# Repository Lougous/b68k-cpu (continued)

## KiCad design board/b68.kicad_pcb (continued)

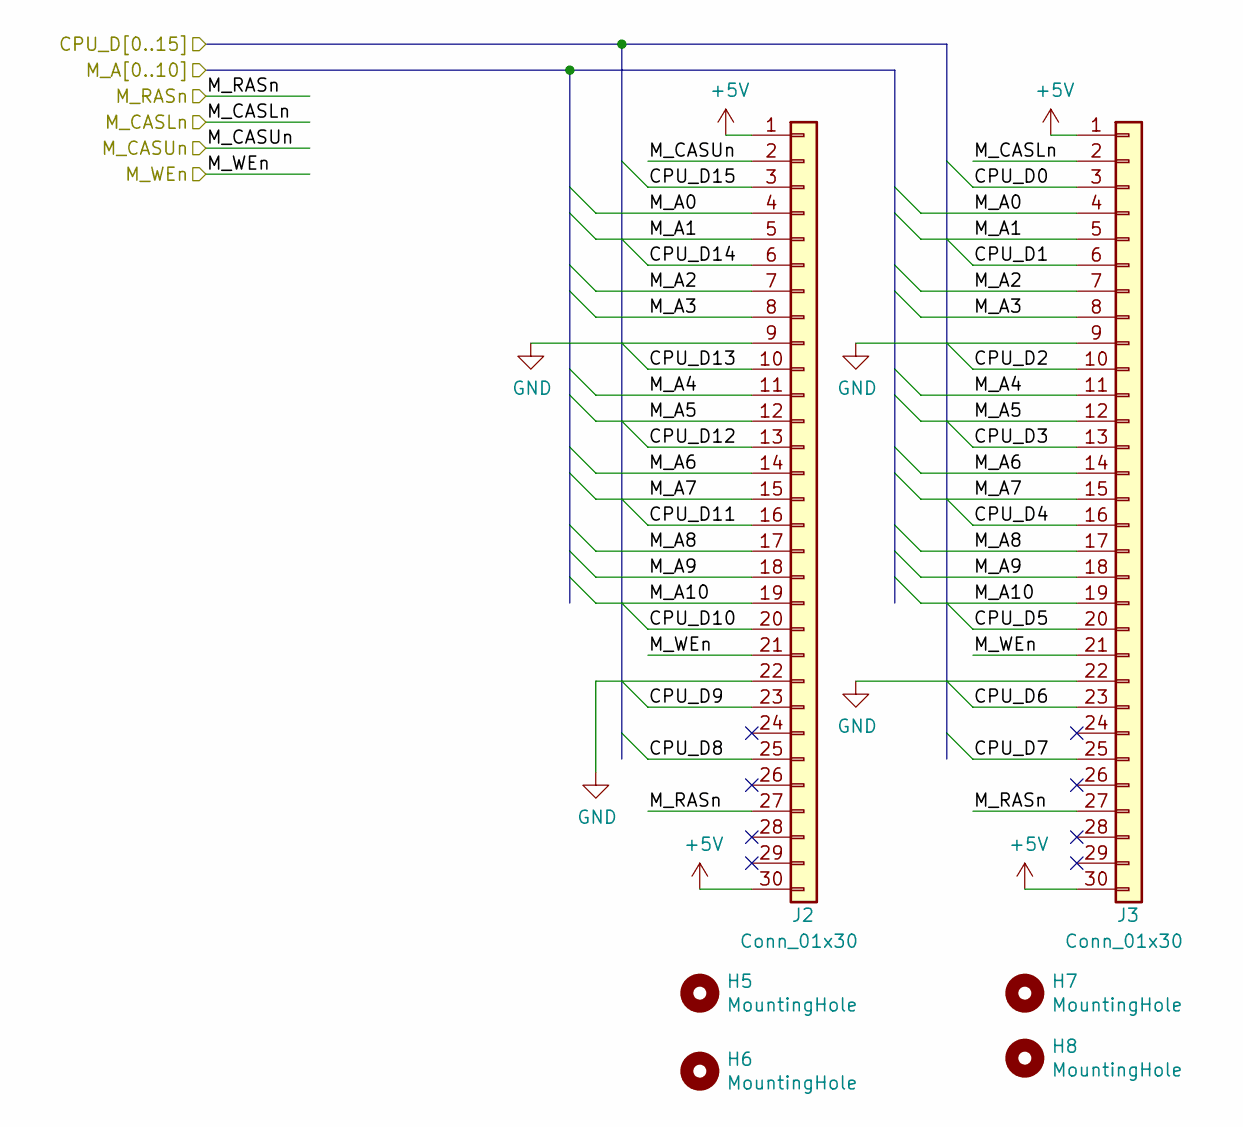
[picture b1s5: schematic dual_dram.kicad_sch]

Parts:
H5, H6, H7, H8: MountingHole; MountingHole_2.7mm_M2.5_DIN965_Pad
J2, J3: Conn_01x30; PinHeader_1x30_P2.54mm_Vertical

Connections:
+5V: J2.1, J2.30, J3.1, J3.30; also elsewhere on the board
/CPU_D0: J3.3; also elsewhere on the board
/CPU_D1: J3.6; also elsewhere on the board
/CPU_D2: J3.10; also elsewhere on the board
/CPU_D3: J3.13; also elsewhere on the board
/CPU_D4: J3.16; also elsewhere on the board
/CPU_D5: J3.20; also elsewhere on the board
/CPU_D6: J3.23; also elsewhere on the board
/CPU_D7: J3.25; also elsewhere on the board
/CPU_D8: J2.25; also elsewhere on the board
/CPU_D9: J2.23; also elsewhere on the board
/CPU_D10: J2.20; also elsewhere on the board
/CPU_D11: J2.16; also elsewhere on the board
/CPU_D12: J2.13; also elsewhere on the board
/CPU_D13: J2.10; also elsewhere on the board
/CPU_D14: J2.6; also elsewhere on the board
/CPU_D15: J2.3; also elsewhere on the board
/M_A0: J2.4, J3.4; also elsewhere on the board
/M_A1: J2.5, J3.5; also elsewhere on the board
/M_A2: J2.7, J3.7; also elsewhere on the board
/M_A3: J2.8, J3.8; also elsewhere on the board
/M_A4: J2.11, J3.11; also elsewhere on the board
/M_A5: J2.12, J3.12; also elsewhere on the board
/M_A6: J2.14, J3.14; also elsewhere on the board
/M_A7: J2.15, J3.15; also elsewhere on the board
/M_A8: J2.17, J3.17; also elsewhere on the board
/M_A9: J2.18, J3.18; also elsewhere on the board
/M_A10: J2.19, J3.19; also elsewhere on the board
/M_CASLn: J3.2; also elsewhere on the board
/M_CASUn: J2.2; also elsewhere on the board
/M_RASn: J2.27, J3.27; also elsewhere on the board
/M_WEn: J2.21, J3.21; also elsewhere on the board
GND: J2.9, J2.22, J3.9, J3.22; also elsewhere on the board

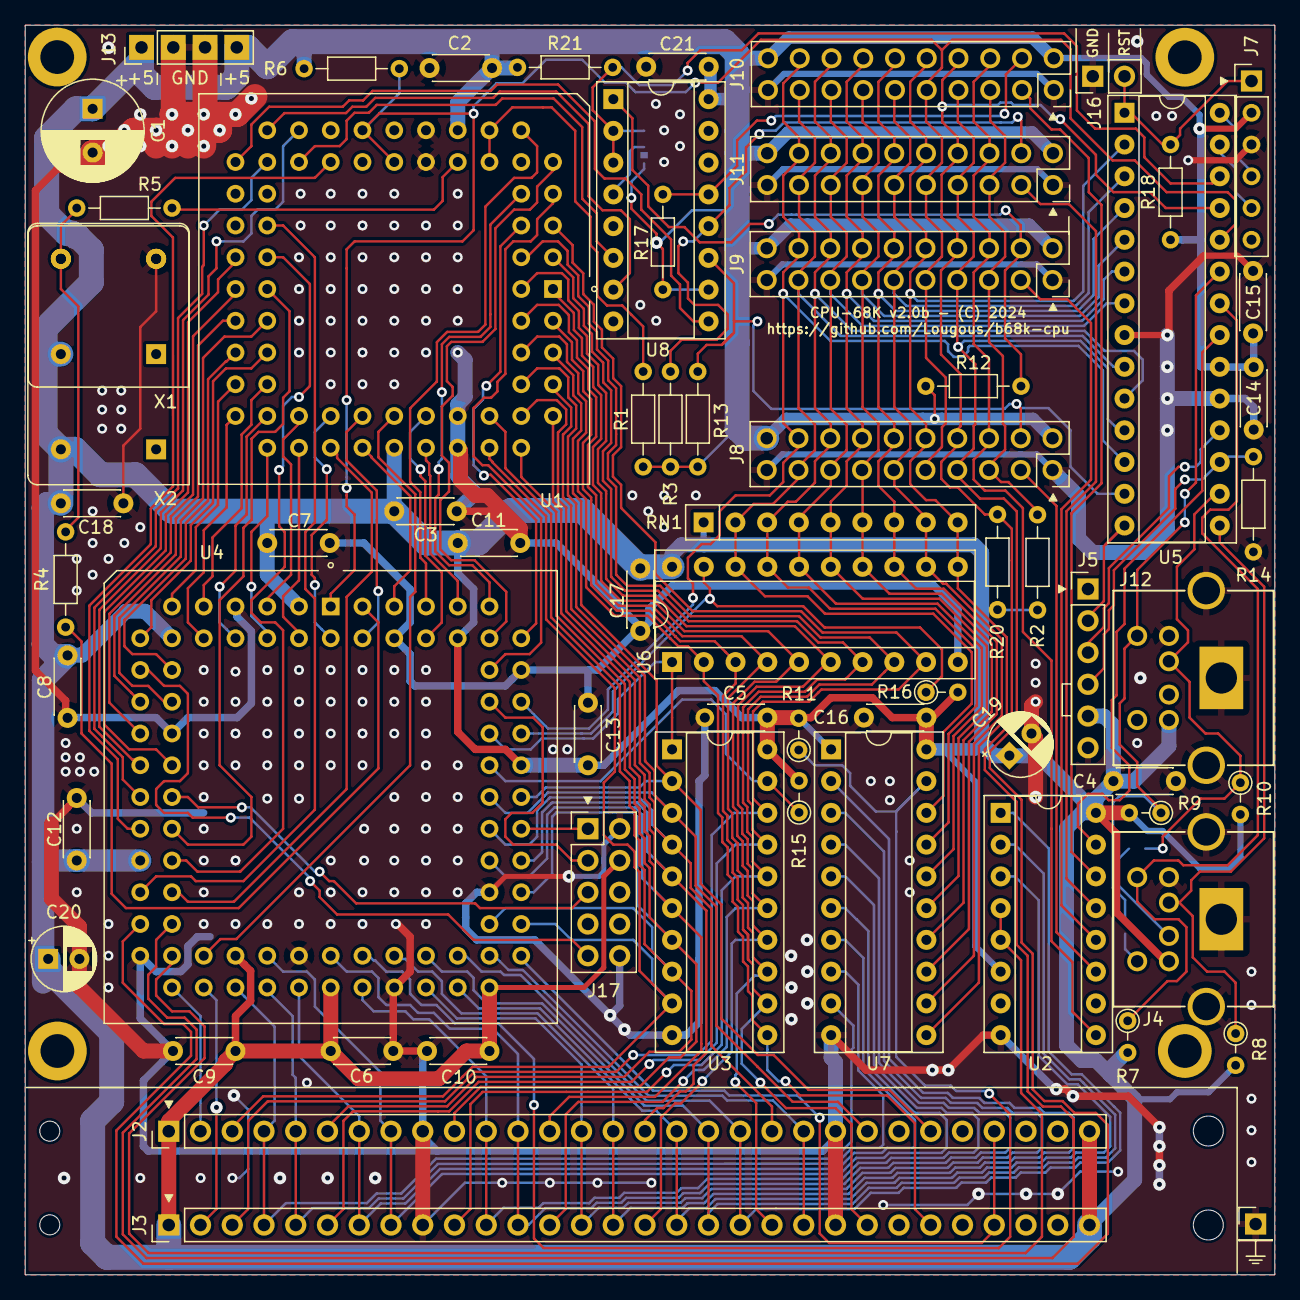
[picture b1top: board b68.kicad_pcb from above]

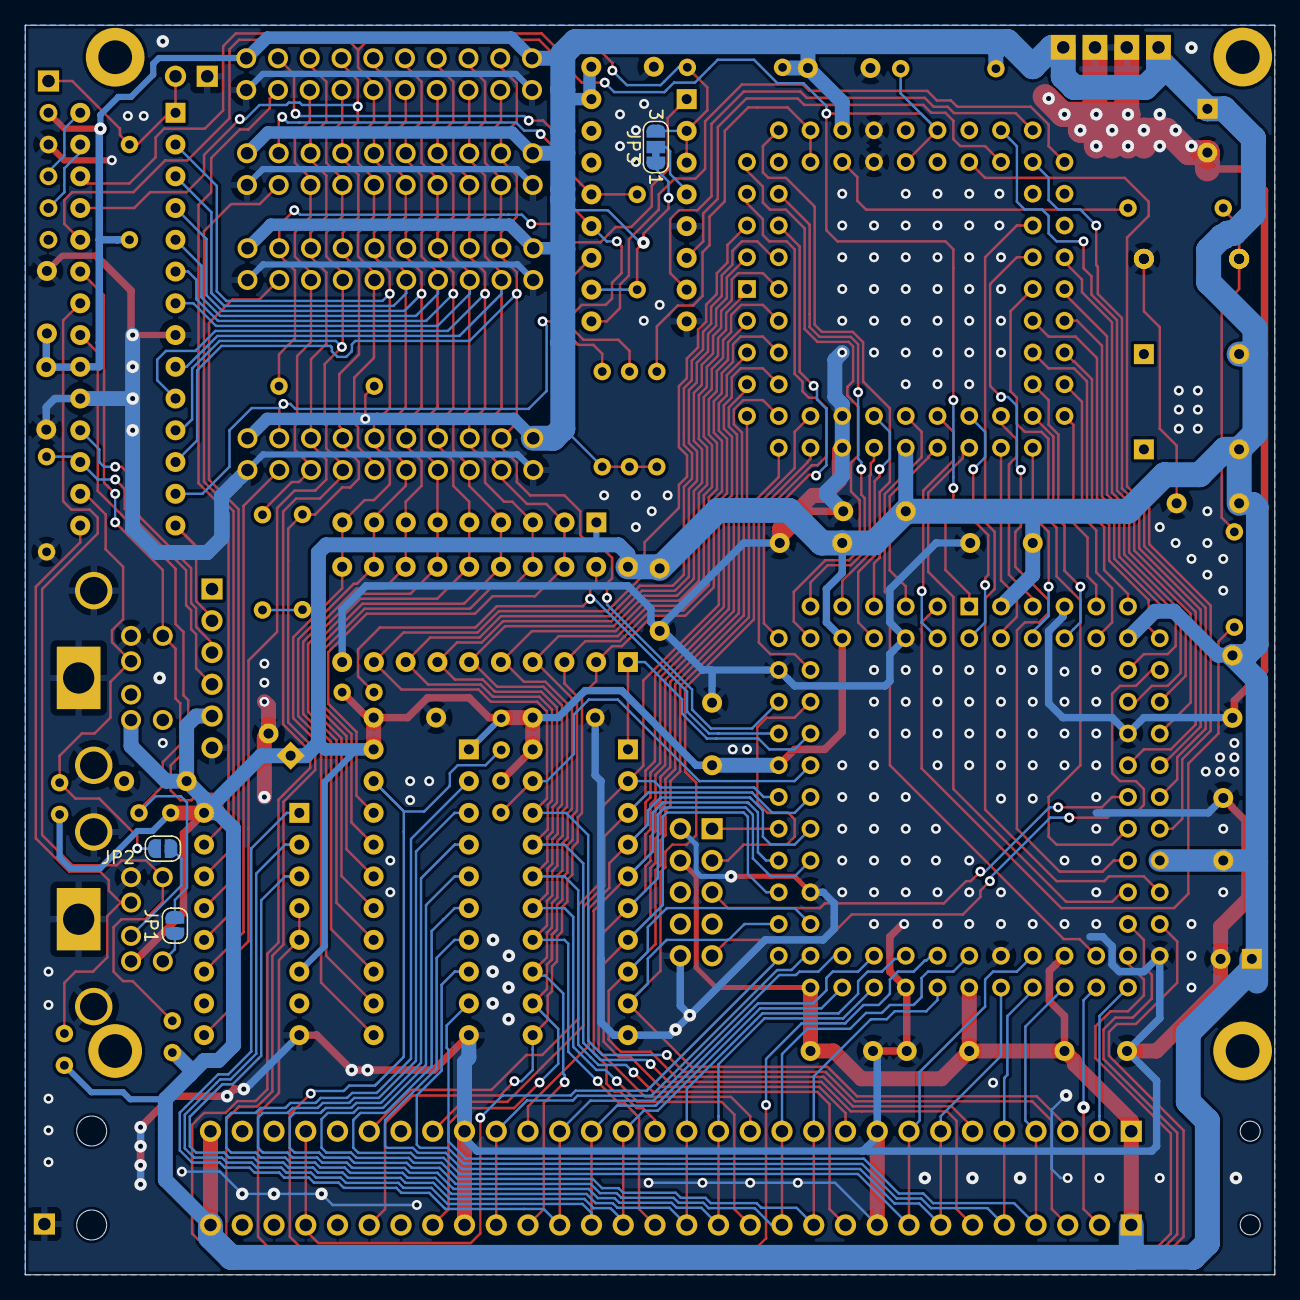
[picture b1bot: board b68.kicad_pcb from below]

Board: 2 copper layers, 100.0 x 100.0 mm, 77 parts (3 on the bottom side), 117 nets.

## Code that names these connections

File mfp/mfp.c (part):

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#pragma config FCMEN = ON       // Fail-Safe Clock Monitor Enable bit (Fail-Safe Clock Monitor enabled)

// CONFIG2L
#pragma config MCLRE = EXTMCLR  // MCLR Enable bit (If LVP = 0, MCLR pin is MCLR; If LVP = 1, RE3 pin function is MCLR )
#pragma config PWRTS = PWRT_OFF // Power-up timer selection bits (PWRT is disabled)
#pragma config MVECEN = ON      // Multi-vector enable bit (Multi-vector enabled, Vector table used for interrupts)
#pragma config IVT1WAY = ON     // IVTLOCK bit One-way set enable bit (IVTLOCK bit can be cleared and set only once)
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    U1TXB = data;                     // send one character
}

#define CEn              (PORTBbits.RB0)

#define RSTn             (PORTBbits.RB3)
#define ASSERT_RSTn      TRISBbits.TRISB3 = 0;   // output - RST# asserted
#define DEASSERT_RSTn    TRISBbits.TRISB3 = 1;   // input - RST# deasserted

#define ACKn             (PORTBbits.RB4)
#define ASSERT_ACKn      TRISBbits.TRISB4 = 0;   // output - ACK# asserted
#define DEASSERT_ACKn    TRISBbits.TRISB4 = 1;   // input - ACK# deasserted

#define IRQn             (PORTBbits.RB5)
#define ASSERT_IRQn      TRISBbits.TRISB5 = 0;   // output - IRQ# asserted
#define DEASSERT_IRQn    TRISBbits.TRISB5 = 1;   // input - IRQ# deasserted

#define WEn              (PORTCbits.RC0)

#define A0               (PORTCbits.RC1)

#define SYS_IRQn             (PORTCbits.RC2)
#define ASSERT_SYS_IRQn      TRISCbits.TRISC2 = 0;   // output - IRQ# asserted
#define DEASSERT_SYS_IRQn    TRISCbits.TRISC2 = 1;   // input - IRQ# deasserted

//#define IOEXT0           (PORTCbits.RC2)
#define IOEXT1           (PORTCbits.RC3)
#define IOEXT2_TX        (PORTCbits.RC7)
#define IOEXT3_RX        (PORTCbits.RC6)

#define BSTP             IOEXT3_RX

#define KB_DAT           (PORTCbits.RC4)
#define KB_CLK           (PORTBbits.RB1)

#define MS_DAT           (PORTCbits.RC5)
#define MS_DAT_DIR       (TRISCbits.TRISC5)

#define MS_CLK           (PORTBbits.RB2)
#define MS_CLK_DIR       (TRISBbits.TRISB2)

// boot file content
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
#if 0
    //set uart 1 pins to extension connector (J5)
    // TX: RC7 (pin 18)
    TRISCbits.TRISC7 = 0;   // output
    RC7PPS=0b00010011;
  
    // RX: RC6 (pin 17)
    TRISCbits.TRISC6 = 1;   // input
    U1RXPPS=0b00010110;
#else
    //set uart 1 pins to debug connector (J7)
    // TX: RB6 (pin 27)
    TRISBbits.TRISB6 = 0;   // output
    RB6PPS=0b00010011;
  
    // RX: RB7 (pin 28)
    TRISBbits.TRISB7 = 1;   // input
    U1RXPPS=0b00001111;    
#endif
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    kbd_dat = 0xffff;
	kbd_sin = 0xffff;

    INT1PPS = 0b01001;  // RB1 (pin 22)
	TRISCbits.TRISC4  = 1;  // RC4 (pin 15) is input (PS/2 data)
    
	INTCON0bits.INT1EDG = 0;  // interrupt on falling edge
//	INTCON0bits.INT1EDG = 1;  // interrupt on rising edge
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	ms_sin = 0xffff;
	ms_recv_mode = 1;
    
    INT2PPS = 0b01010;   // RB2 (pin 23)
    LATBbits.LATB2 = 0;  // PS/2 clock : GND = asserted (when output)
	MS_DAT_DIR     = 1;  // RC5 (pin 16) is input (PS/2 data)
    LATBbits.LATB5 = 0;  // PS/2 data : GND = asserted (when output)
    
	INTCON0bits.INT2EDG = 0;  // interrupt on falling edge
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
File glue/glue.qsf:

# -------------------------------------------------------------------------- #
#
# Copyright (C) 1991-2013 Altera Corporation
# Your use of Altera Corporation's design tools, logic functions 
# and other software and tools, and its AMPP partner logic 
# functions, and any output files from any of the foregoing 
# (including device programming or simulation files), and any 
# associated documentation or information are expressly subject 
# to the terms and conditions of the Altera Program License 
# Subscription Agreement, Altera MegaCore Function License 
# Agreement, or other applicable license agreement, including, 
# without limitation, that your use is for the sole purpose of 
# programming logic devices manufactured by Altera and sold by 
# Altera or its authorized distributors.  Please refer to the 
# applicable agreement for further details.
#
# -------------------------------------------------------------------------- #
#
# Quartus II 32-bit
# Version 13.0.1 Build 232 06/12/2013 Service Pack 1 SJ Web Edition
# Date created = 21:01:15  November 10, 2020
#
# -------------------------------------------------------------------------- #
#
# Notes:
#
# 1) The default values for assignments are stored in the file:
#		glue_assignment_defaults.qdf
#    If this file doesn't exist, see file:
#		assignment_defaults.qdf
#
# 2) Altera recommends that you do not modify this file. This
#    file is updated automatically by the Quartus II software
#    and any changes you make may be lost or overwritten.
#
# -------------------------------------------------------------------------- #

# global settings
set_global_assignment -name FAMILY MAX7000S
set_global_assignment -name DEVICE "EPM7128SLC84-10"
set_global_assignment -name TOP_LEVEL_ENTITY glue
set_global_assignment -name ORIGINAL_QUARTUS_VERSION "13.0 SP1"
set_global_assignment -name PROJECT_CREATION_TIME_DATE "21:01:15  NOVEMBER 10, 2020"
set_global_assignment -name LAST_QUARTUS_VERSION "13.0 SP1"
set_global_assignment -name PROJECT_OUTPUT_DIRECTORY output_files
set_global_assignment -name DEVICE_FILTER_PACKAGE PLCC
set_global_assignment -name DEVICE_FILTER_PIN_COUNT 84
set_global_assignment -name DEVICE_FILTER_SPEED_GRADE 10
set_global_assignment -name ERROR_CHECK_FREQUENCY_DIVISOR "-1"
set_global_assignment -name MAX7000_DEVICE_IO_STANDARD TTL
set_global_assignment -name OPTIMIZE_HOLD_TIMING OFF
set_global_assignment -name OPTIMIZE_MULTI_CORNER_TIMING OFF
set_global_assignment -name FITTER_EFFORT "STANDARD FIT"
set_global_assignment -name RESERVE_ALL_UNUSED_PINS_NO_OUTPUT_GND "AS INPUT TRI-STATED"
set_global_assignment -name POWER_USE_PVA OFF
set_global_assignment -name FORCE_FITTER_TO_AVOID_PERIPHERY_PLACEMENT_WARNINGS ON

# file(s)
set_global_assignment -name VHDL_FILE glue.vhd

# pinout
set_location_assignment PIN_83 -to GCLK
set_location_assignment PIN_1 -to RSTn

set_location_assignment PIN_31 -to B_ACKn
set_location_assignment PIN_30 -to B_WEn
set_location_assignment PIN_70 -to B_A0
set_location_assignment PIN_68 -to G_OEn_LO
set_location_assignment PIN_67 -to G_OEn
set_location_assignment PIN_34 -to G_CSn
set_location_assignment PIN_69 -to G_DIR
set_location_assignment PIN_46 -to G_OEn_HI

set_location_assignment PIN_22 -to CPU_FC2
set_location_assignment PIN_80 -to CPU_A[23]
set_location_assignment PIN_77 -to CPU_A[22]
set_location_assignment PIN_36 -to CPU_A[21]
set_location_assignment PIN_84 -to CPU_A[20]
set_location_assignment PIN_81 -to CPU_A[19]
set_location_assignment PIN_2 -to CPU_A[18]
set_location_assignment PIN_29 -to CPU_A[17]
set_location_assignment PIN_5 -to CPU_A[16]
set_location_assignment PIN_4 -to CPU_A[15]
set_location_assignment PIN_8 -to CPU_A[14]
set_location_assignment PIN_6 -to CPU_A[13]
set_location_assignment PIN_10 -to CPU_A[12]
set_location_assignment PIN_9 -to CPU_A[11]
set_location_assignment PIN_11 -to CPU_A[10]
set_location_assignment PIN_12 -to CPU_A[9]
set_location_assignment PIN_15 -to CPU_A[8]
set_location_assignment PIN_17 -to CPU_A[7]
set_location_assignment PIN_16 -to CPU_A[6]
set_location_assignment PIN_25 -to CPU_A[5]
set_location_assignment PIN_18 -to CPU_A[4]
set_location_assignment PIN_27 -to CPU_A[3]
set_location_assignment PIN_21 -to CPU_A[2]
set_location_assignment PIN_28 -to CPU_A[1]
set_location_assignment PIN_74 -to CPU_ASn
set_location_assignment PIN_20 -to CPU_BERRn
set_location_assignment PIN_56 -to CPU_D[15]
set_location_assignment PIN_57 -to CPU_D[14]
set_location_assignment PIN_58 -to CPU_D[13]
set_location_assignment PIN_61 -to CPU_D[12]
set_location_assignment PIN_60 -to CPU_D[11]
set_location_assignment PIN_63 -to CPU_D[10]
set_location_assignment PIN_65 -to CPU_D[9]
set_location_assignment PIN_64 -to CPU_D[8]
set_location_assignment PIN_76 -to CPU_RWn
set_location_assignment PIN_75 -to CPU_LDSn
set_location_assignment PIN_73 -to CPU_UDSn
set_location_assignment PIN_24 -to CPU_VPAn
set_location_assignment PIN_79 -to CPU_DTACKn

set_location_assignment PIN_52 -to M_A[10]
set_location_assignment PIN_50 -to M_A[9]
set_location_assignment PIN_51 -to M_A[8]
set_location_assignment PIN_48 -to M_A[7]
set_location_assignment PIN_49 -to M_A[6]
set_location_assignment PIN_44 -to M_A[5]
set_location_assignment PIN_45 -to M_A[4]
set_location_assignment PIN_40 -to M_A[3]
set_location_assignment PIN_41 -to M_A[2]
set_location_assignment PIN_39 -to M_A[1]
set_location_assignment PIN_37 -to M_A[0]
set_location_assignment PIN_35 -to M_CASLn
set_location_assignment PIN_33 -to M_CASUn
set_location_assignment PIN_54 -to M_RASn
set_location_assignment PIN_55 -to M_WEn

# generate post-layout model
set_global_assignment -name EDA_SIMULATION_TOOL "ModelSim-Altera (VHDL)"
set_global_assignment -name EDA_OUTPUT_DATA_FORMAT VHDL -section_id eda_simulation

# timing
set_instance_assignment -name CUT ON -from reg_pmu_mask[*] -to pmu_access_error
set_global_assignment -name FMAX_REQUIREMENT "20 MHz" -section_id GCLK
set_instance_assignment -name CLOCK_SETTINGS GCLK -to GCLK

set_instance_assignment -name STATE_MACHINE_PROCESSING AUTO -to s_state

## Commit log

2024-05-20 Create LICENSE
2024-05-20 add board picture
2024-05-20 import CBA files
2024-05-20 add documentation
2024-05-29 ignore .kicad_prl files (local settings)
2024-05-29 import glue CPLD files
2024-05-29 documentation
2024-05-29 import MFP files
2024-06-11 add some filters
2024-06-11 more description
2024-06-11 fix U5 part
2024-06-22 filter out MPLAB generated files
2024-06-22 fix path to 68k software binary images
2024-07-06 enable debug mode with D key
2024-07-06 upgrade MPLAB / xc8 versions + enable optimizations
2024-07-09 fix memory mapping and part list
2024-08-26 use VHDL case structure to implement FSM
